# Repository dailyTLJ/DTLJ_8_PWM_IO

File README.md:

# DTLJ_8_PWM_IO
custom Arduino Mega Shield

8 Molex 4-c connectors, each connected to power, ground, PWM (2-9) and Analog Input (8-15)

## Version 2
Inline resistor (smd 1206) on PWM lines

## Version 3
Inline resistors (smd 1206) on PWM lines and pull-down resistors (smd 1206) on Analog input lines

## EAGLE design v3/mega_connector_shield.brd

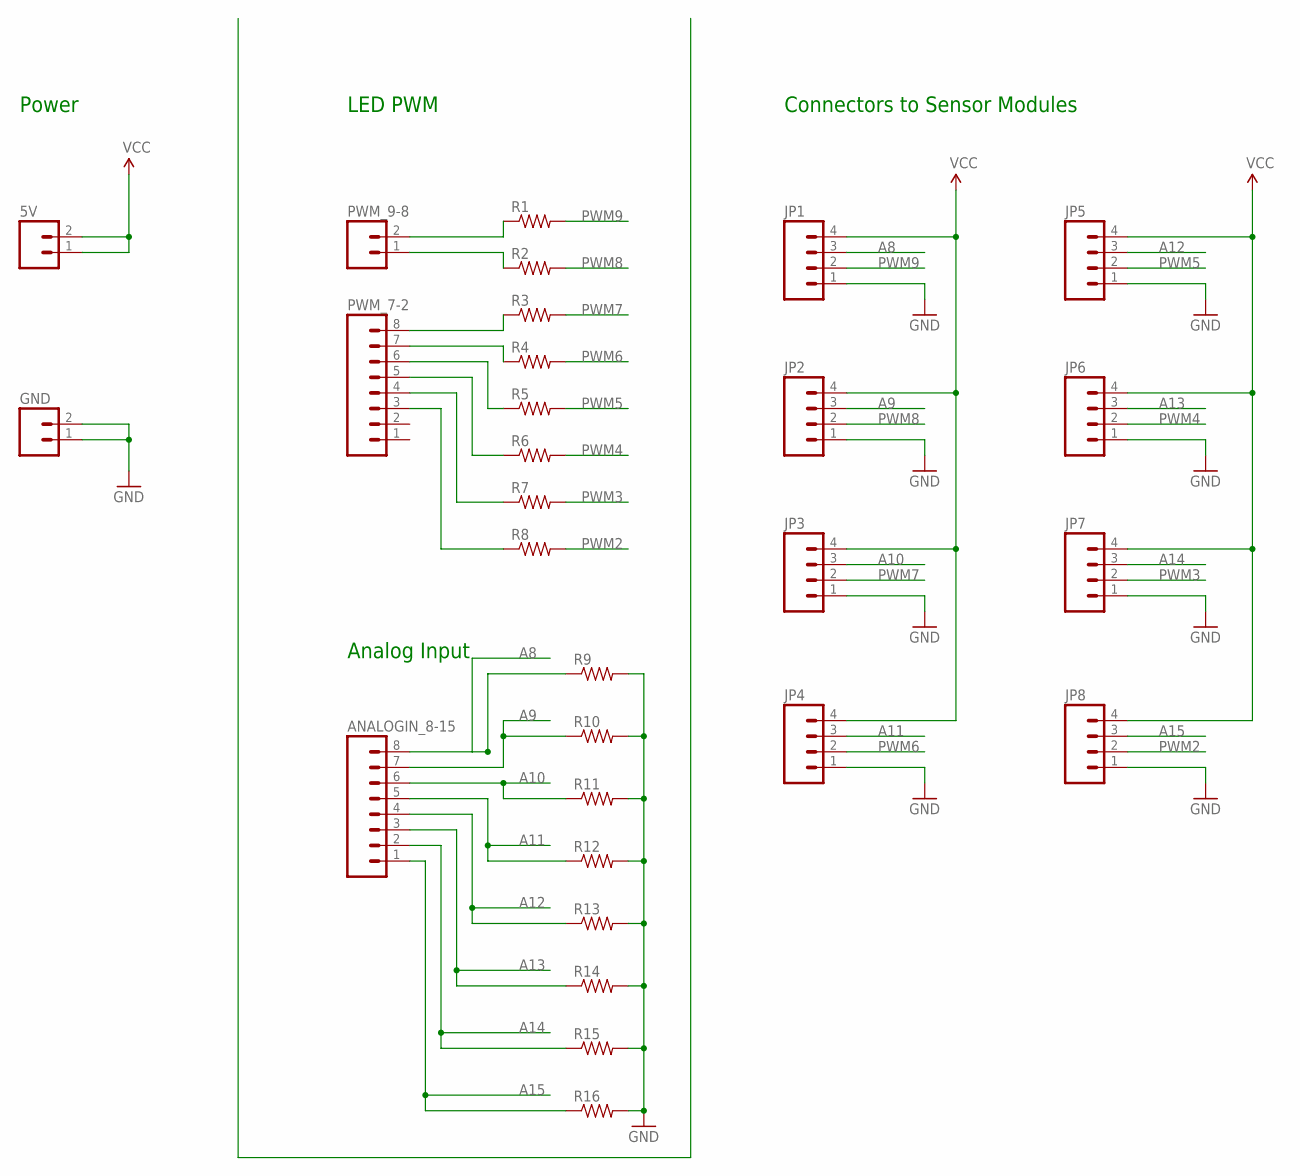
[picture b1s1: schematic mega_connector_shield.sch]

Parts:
5V: M02PTH; 1X02
ANALOGIN_8-15: M08; 1X08_ROUND
GND: M02PTH; 1X02
JP1, JP2, JP3, JP4, JP5, JP6, JP7, JP8: M04POLAR; MOLEX-1X4
PWM_7-2: M08; 1X08_ROUND
PWM_9-8: M02PTH; 1X02
R1, R2, R3, R4, R5, R6, R7, R8, R9, R10, R11, R12, R13, R14, R15, R16: RESISTOR1206; 1206

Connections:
A8: ANALOGIN_8-15.8, JP1.3, R9.1
A9: ANALOGIN_8-15.7, JP2.3, R10.1
A10: ANALOGIN_8-15.6, JP3.3, R11.1
A11: ANALOGIN_8-15.5, JP4.3, R12.1
A12: ANALOGIN_8-15.4, JP5.3, R13.1
A13: ANALOGIN_8-15.3, JP6.3, R14.1
A14: ANALOGIN_8-15.2, JP7.3, R15.1
A15: ANALOGIN_8-15.1, JP8.3, R16.1
GND: GND.1, GND.2, JP1.1, JP2.1, JP3.1, JP4.1, JP5.1, JP6.1, JP7.1, JP8.1, R9.2, R10.2, R11.2, R12.2, R13.2, R14.2, R15.2, R16.2
unnamed: PWM_9-8.2, R1.1
unnamed: PWM_9-8.1, R2.1
unnamed: PWM_7-2.8, R3.1
unnamed: PWM_7-2.7, R4.1
unnamed: PWM_7-2.6, R5.1
unnamed: PWM_7-2.5, R6.1
unnamed: PWM_7-2.4, R7.1
unnamed: PWM_7-2.3, R8.1
PWM2: JP8.2, R8.2
PWM3: JP7.2, R7.2
PWM4: JP6.2, R6.2
PWM5: JP5.2, R5.2
PWM6: JP4.2, R4.2
PWM7: JP3.2, R3.2
PWM8: JP2.2, R2.2
PWM9: JP1.2, R1.2
VCC: 5V.1, 5V.2, JP1.4, JP2.4, JP3.4, JP4.4, JP5.4, JP6.4, JP7.4, JP8.4

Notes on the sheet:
Power
LED PWM
Analog Input
Connectors to Sensor Modules

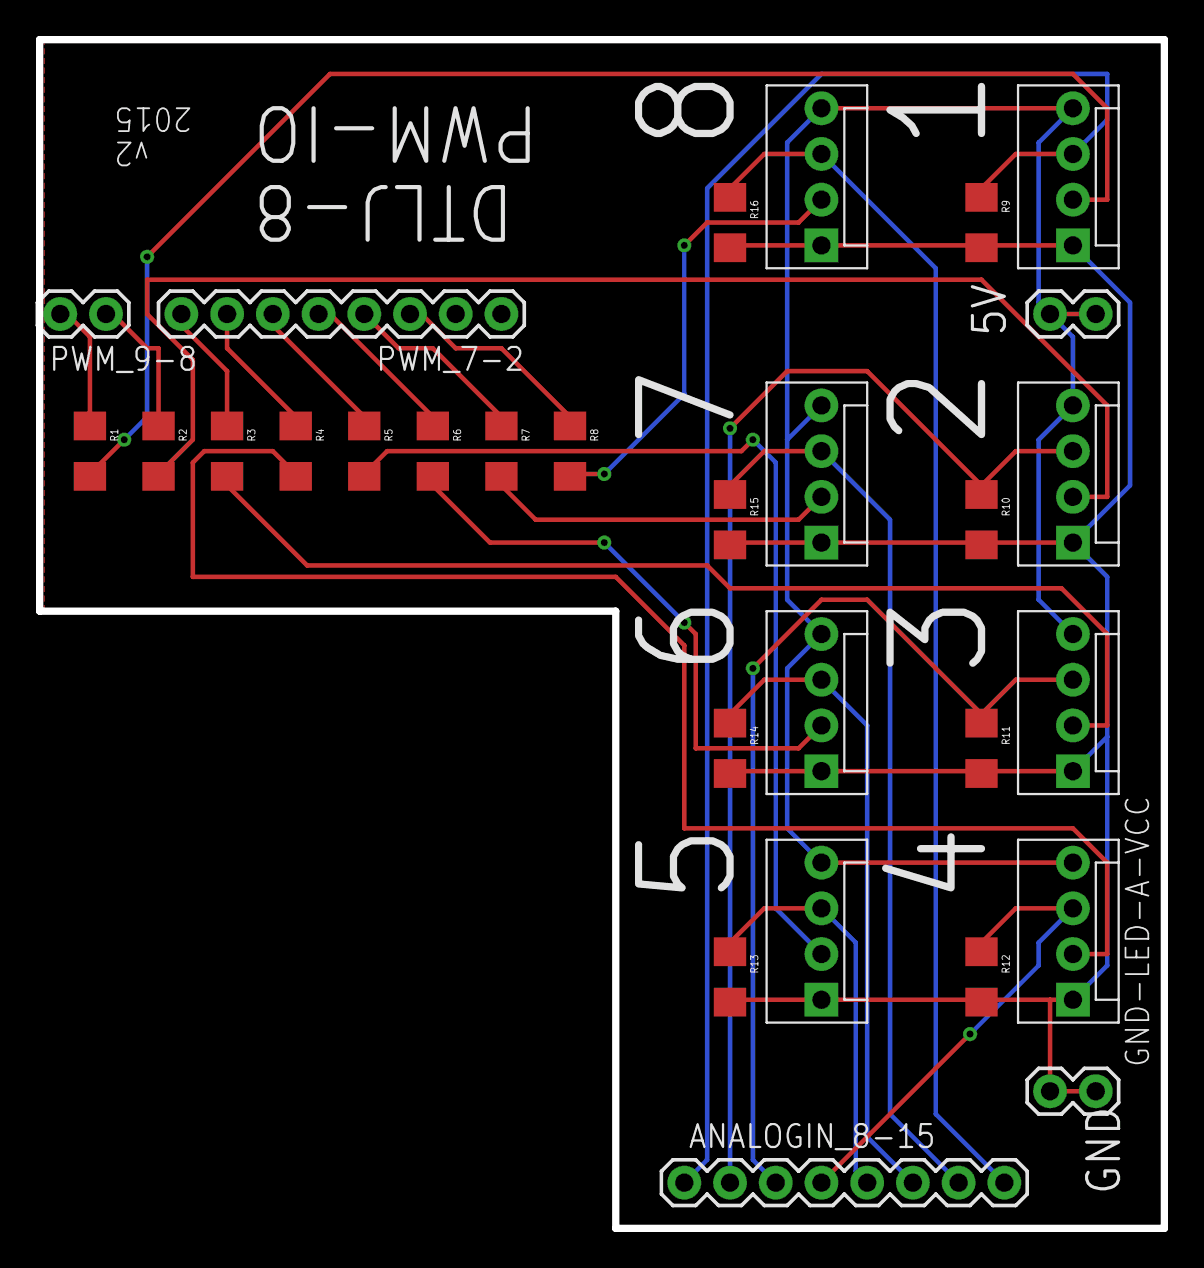
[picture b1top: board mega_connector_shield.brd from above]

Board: 2 copper layers, 62.5 x 66.0 mm, 29 parts (0 on the bottom side), 26 nets.

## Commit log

2015-08-21 first version ready to order
2015-09-15 change shape, add sensor resistor here for pull-down when not connected
2016-09-08 board pngs and demo circuit of full sensor/led circuit

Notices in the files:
parts and their libraries:
SparkFun-Connectors: Licensing: Creative Commons ShareAlike 4.0 International - https://creativecommons.org/licenses/by-sa/4.0
